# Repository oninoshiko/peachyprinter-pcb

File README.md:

This is just the production version of the Peachy Printer PCB, converted from Eagle format to Kicad.

Thanks to:

Rylan Grayston and the Peachy Team (for opening-sourceing, not just the 
					software, but the entire peachy design)

lachlanA (for the eagle to kicad conversion ULP)

Erich Heine (for the eagle half of the conversion)

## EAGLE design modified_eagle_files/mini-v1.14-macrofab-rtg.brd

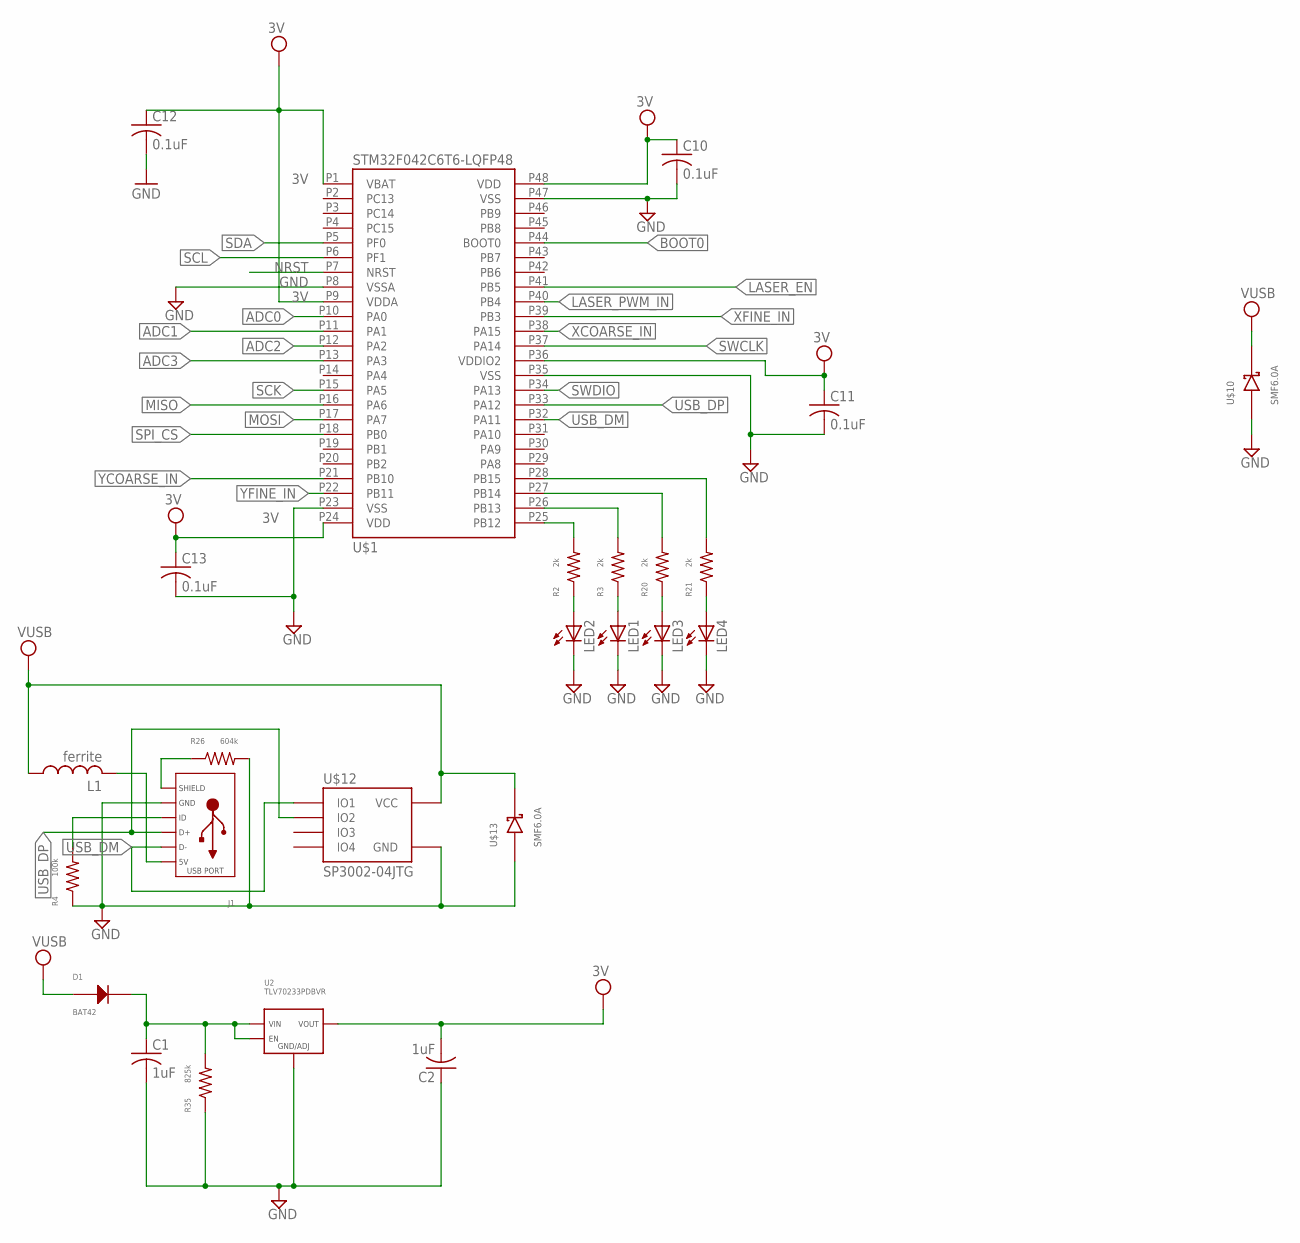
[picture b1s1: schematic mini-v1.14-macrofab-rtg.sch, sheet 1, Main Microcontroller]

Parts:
C1, C2: 1uF; C0603
C10, C11, C12, C13: 0.1uF; C0603
D1: BAT42; SOD-123
J1: USB_MICRO_RIGHT; MICROUSB-RIGHT
L1: ferrite; C0603
LED1, LED2, LED3, LED4: LEDCHIP-LED0603; CHIP-LED0603
R2, R3, R20, R21: 2k; R0603
R4: 100k; R0603
R26: 604k; R0603
R35: 825k; R0603
U2: TLV70233PDBVR; SOT-23-5
U$1: STM32F042C6T6-LQFP48; LQFP48
U$10, U$13: SMF6.0A; SOD123
U$12: SP3002-04JTG; SC70-6

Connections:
3V: C2.2, C10.1, C11.1, C12.1, C13.1, U2.P$5 (VOUT), U$1.P1 (VBAT), U$1.P9 (VDDA), U$1.P24 (VDD), U$1.P36 (VDDIO2), U$1.P48 (VDD); also elsewhere on the board
ADC0: U$1.P10 (PA0); also elsewhere on the board
ADC1: U$1.P11 (PA1); also elsewhere on the board
ADC2: U$1.P12 (PA2); also elsewhere on the board
ADC3: U$1.P13 (PA3); also elsewhere on the board
BOOT0: U$1.P44 (BOOT0); also elsewhere on the board
GND: C1.2, C2.1, C10.2, C11.2, C12.2, C13.2, J1.5 (GND), LED1.C, LED2.C, LED3.C, LED4.C, R4.P$1, R26.P$2, R35.P$1, U2.P$2 (GND/ADJ), U$1.P8 (VSSA), U$1.P23 (VSS), U$1.P35 (VSS), U$1.P47 (VSS), U$10.ANODE, U$12.P2 (GND), U$13.ANODE; also elsewhere on the board
LASER_EN: U$1.P41 (PB5); also elsewhere on the board
LASER_PWM_IN: U$1.P40 (PB4); also elsewhere on the board
MISO: U$1.P16 (PA6); also elsewhere on the board
MOSI: U$1.P17 (PA7); also elsewhere on the board
unnamed: R2.P$2, U$1.P25 (PB12)
unnamed: LED2.A, R2.P$1
unnamed: C1.1, D1.CATHODE, R35.P$2, U2.P$1 (VIN), U2.P$3 (EN)
unnamed: J1.4 (ID), R4.P$2
unnamed: LED1.A, R3.P$1
unnamed: R3.P$2, U$1.P26 (PB13)
unnamed: J1.1 (5V), L1.2
unnamed: J1.S1 (SLD), J1.S2 (SLD), J1.S3 (SLD), J1.S4 (SLD), J1.S5 (SLD), J1.S6 (SLD), R26.P$1
unnamed: LED3.A, R20.P$1
unnamed: LED4.A, R21.P$1
unnamed: R20.P$2, U$1.P27 (PB14)
unnamed: R21.P$2, U$1.P28 (PB15)
NRST: U$1.P7 (NRST); also elsewhere on the board
SCK: U$1.P15 (PA5); also elsewhere on the board
SCL: U$1.P6 (PF1); also elsewhere on the board
SDA: U$1.P5 (PF0); also elsewhere on the board
SPI_CS: U$1.P18 (PB0); also elsewhere on the board
SWCLK: U$1.P37 (PA14); also elsewhere on the board
SWDIO: U$1.P34 (PA13); also elsewhere on the board
USB_DM: J1.2 (D-), U$1.P32 (PA11), U$12.P1 (IO1)
USB_DP: J1.3 (D+), U$1.P33 (PA12), U$12.P3 (IO2)
VUSB: D1.ANODE, L1.1, U$10.CATHODE, U$12.P5 (VCC), U$13.CATHODE; also elsewhere on the board
XCOARSE_IN: U$1.P38 (PA15); also elsewhere on the board
XFINE_IN: U$1.P39 (PB3); also elsewhere on the board
YCOARSE_IN: U$1.P21 (PB10); also elsewhere on the board
YFINE_IN: U$1.P22 (PB11); also elsewhere on the board

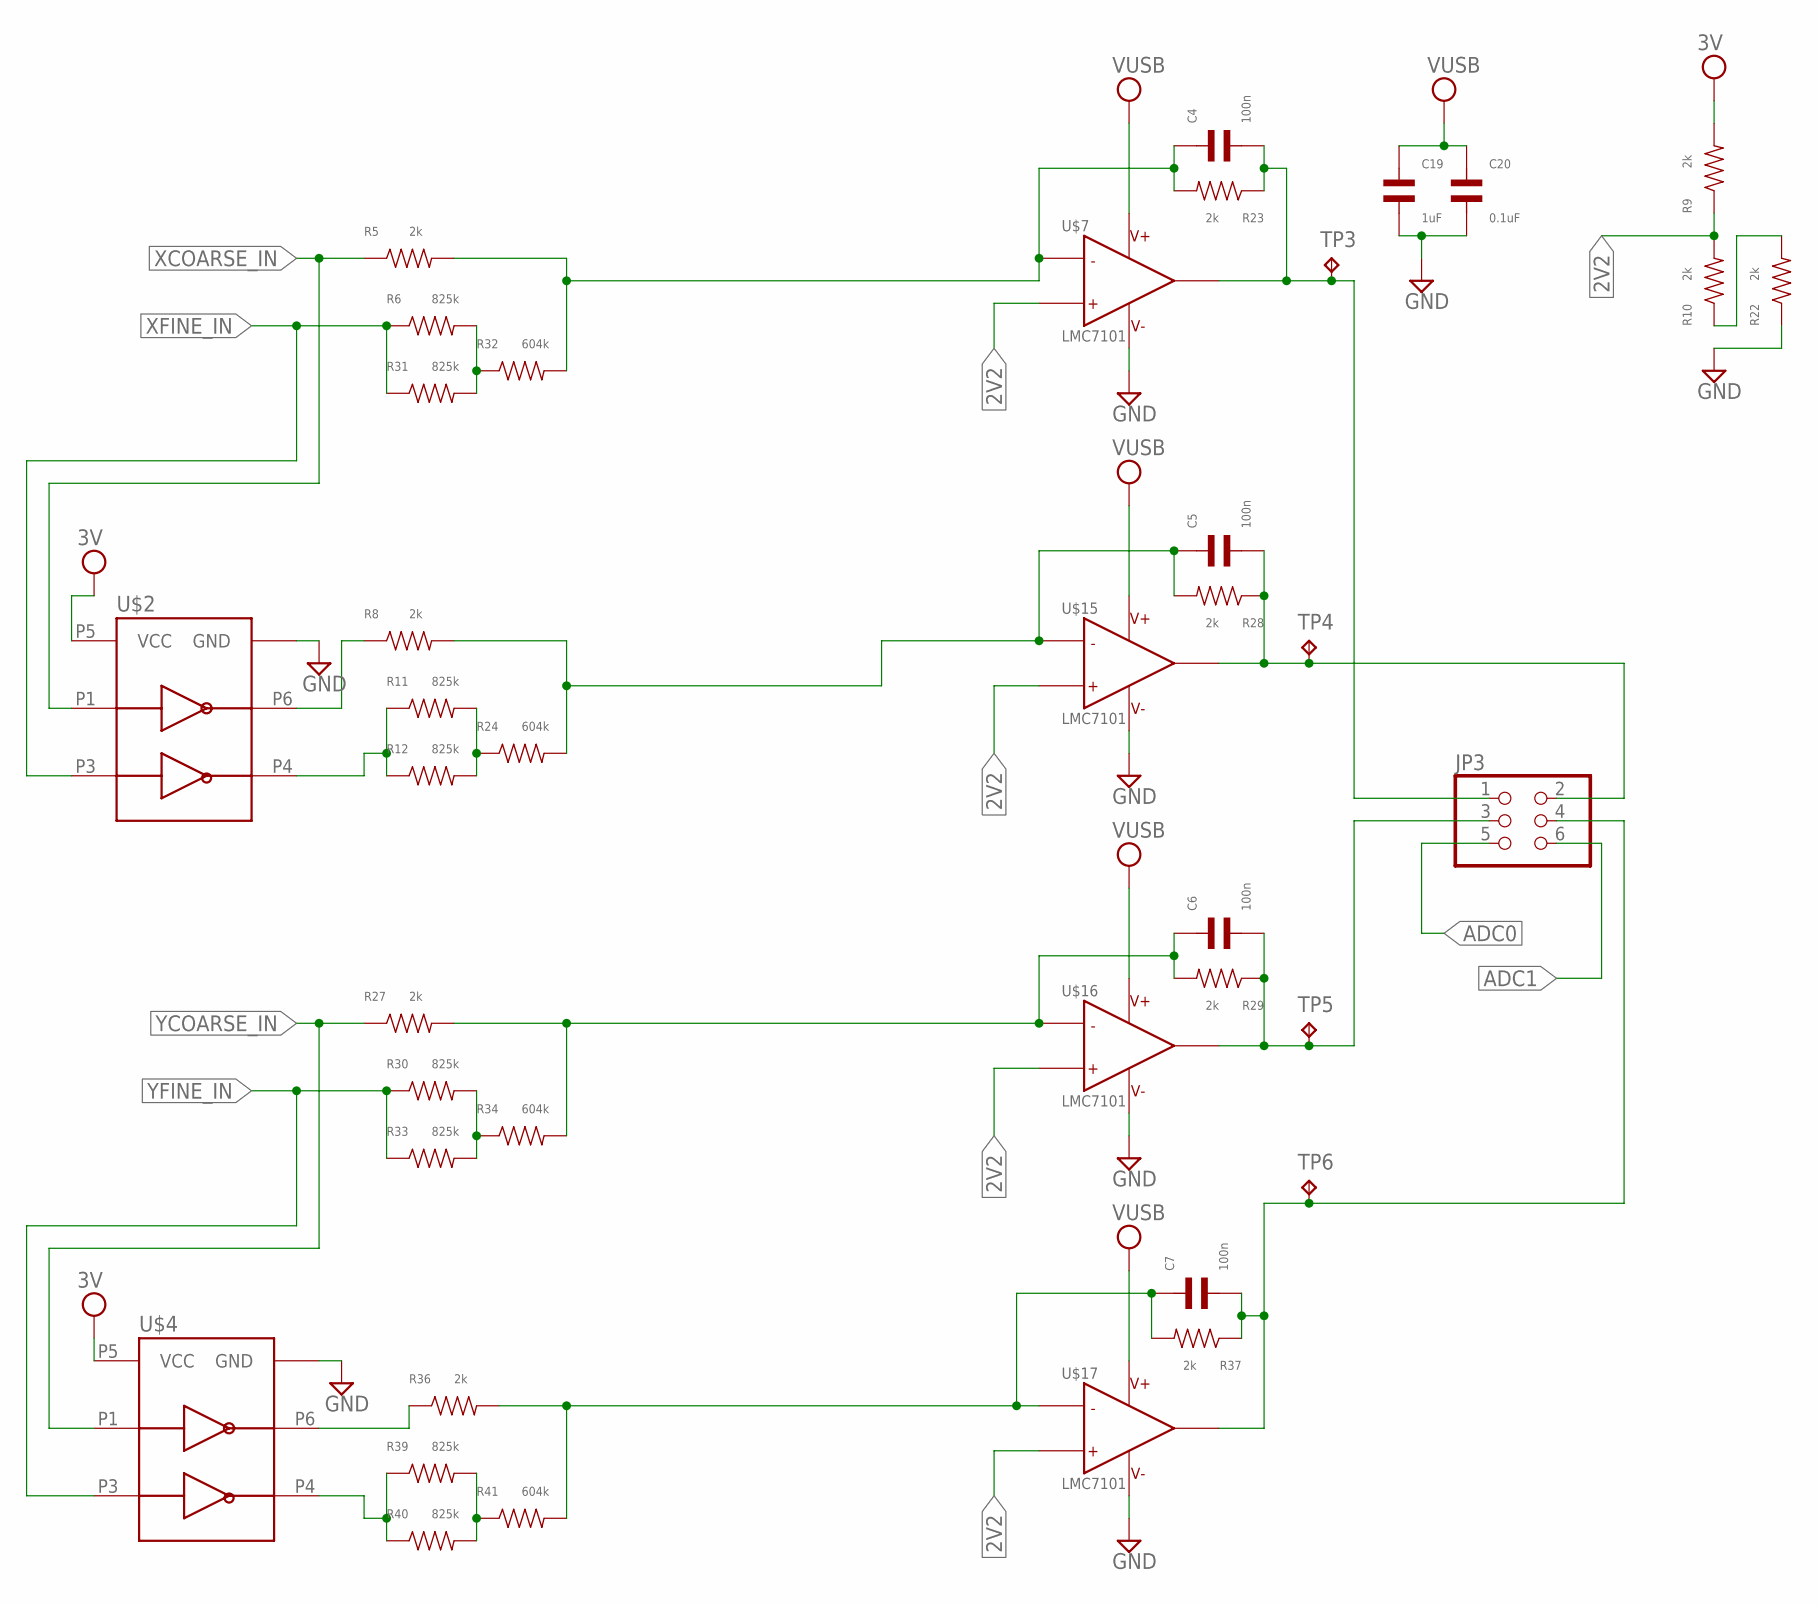
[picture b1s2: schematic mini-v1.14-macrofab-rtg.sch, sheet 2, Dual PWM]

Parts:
C4, C5, C6, C7: 100n; C0603
C19: 1uF; C0603
C20: 0.1uF; C0603
JP3: PINHD-2X3; 2X03
R5, R8, R9, R10, R22, R23, R27, R28, R29, R36, R37: 2k; R0603
R6, R11, R12, R30, R31, R33, R39, R40: 825k; R0603
R24, R32, R34, R41: 604k; R0603
TP3, TP4, TP5, TP6: TPB1,27; B1,27
U$2, U$4: NC7WZ14P6X; SC70-6
U$7, U$15, U$16, U$17: LMC7101; SOT23-5

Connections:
2V2: R9.P$1, R10.P$2, U$7.3, U$15.3, U$16.3, U$17.3
3V: R9.P$2, U$2.P5 (VCC), U$4.P5 (VCC); also elsewhere on the board
ADC0: JP3.5; also elsewhere on the board
ADC1: JP3.6; also elsewhere on the board
COARSE1: R8.P$1, U$2.P6 (Y1)
FINE1: R11.P$1, R12.P$1, U$2.P4 (Y2)
FINE3: R39.P$1, R40.P$1, U$4.P4 (Y2)
GND: C19.P$2, C20.P$2, R22.P$1, U$2.P2 (GND), U$4.P2 (GND), U$7.5, U$15.5, U$16.5, U$17.5; also elsewhere on the board
unnamed: R36.P$1, U$4.P6 (Y1)
unnamed: R11.P$2, R12.P$2, R24.P$1
unnamed: C5.P$1, R8.P$2, R24.P$2, R28.P$2, U$15.4
unnamed: R10.P$1, R22.P$2
unnamed: R30.P$2, R33.P$2, R34.P$1
unnamed: R6.P$2, R31.P$2, R32.P$1
unnamed: C6.P$1, R27.P$2, R29.P$2, R34.P$2, U$16.4
unnamed: R39.P$2, R40.P$2, R41.P$1
unnamed: C7.P$1, R36.P$2, R37.P$2, R41.P$2, U$17.4
OUT: C4.P$2, JP3.1, R23.P$1, TP3.TP, U$7.1
OUT1: C5.P$2, JP3.2, R28.P$1, TP4.TP, U$15.1
OUT2: C6.P$2, JP3.3, R29.P$1, TP5.TP, U$16.1
OUT3: C7.P$2, JP3.4, R37.P$1, TP6.TP, U$17.1
VUSB: C19.P$1, C20.P$1, U$7.2, U$15.2, U$16.2, U$17.2; also elsewhere on the board
XCOARSE_IN: R5.P$1, U$2.P1 (A1); also elsewhere on the board
XFINE_IN: R6.P$1, R31.P$1, U$2.P3 (A2); also elsewhere on the board
XSUM: C4.P$1, R5.P$2, R23.P$2, R32.P$2, U$7.4
YCOARSE_IN: R27.P$1, U$4.P1 (A1); also elsewhere on the board
YFINE_IN: R30.P$1, R33.P$1, U$4.P3 (A2); also elsewhere on the board

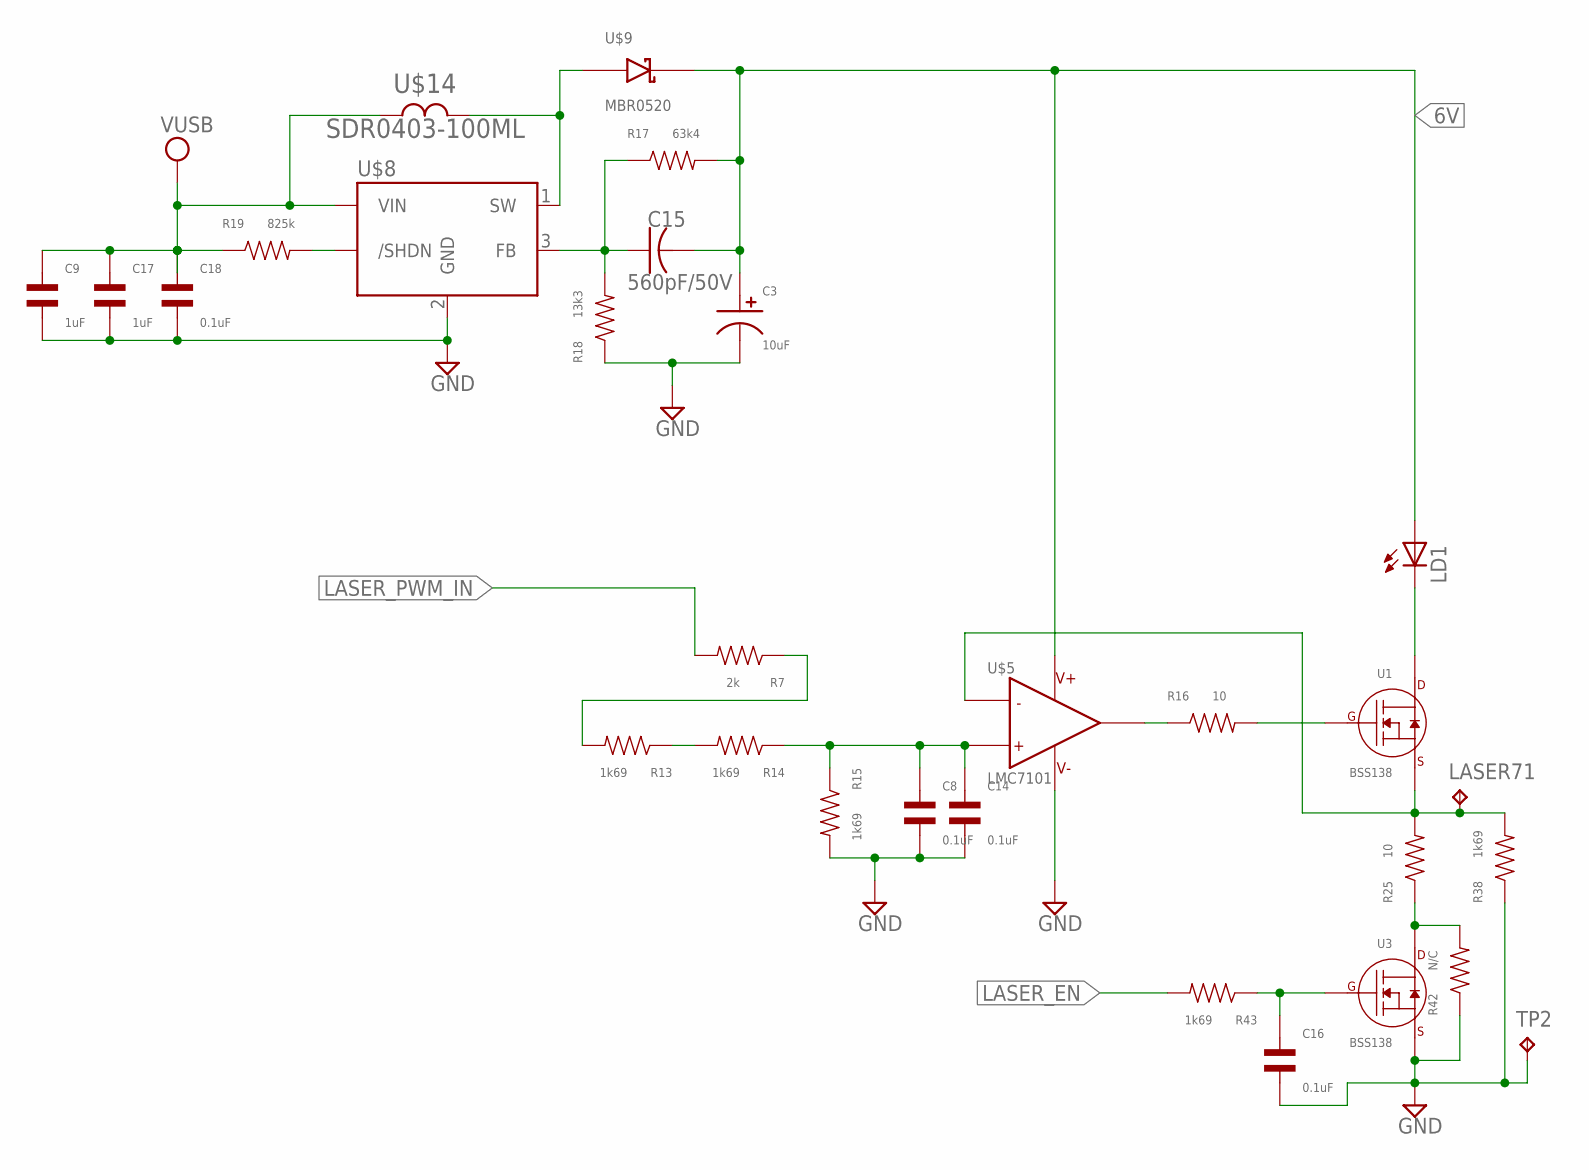
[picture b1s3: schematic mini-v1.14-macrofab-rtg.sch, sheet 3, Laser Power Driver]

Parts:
C3: 10uF; CP4MM
C8, C14, C16, C18: 0.1uF; C0603
C9, C17: 1uF; C0603
C15: 560pF/50V; C0603
LASER71: TPB2,54; B2,54
LD1: SCOTT_LASERDIODELD3; SCOTT_LASERDIODE3; MPN 3 x (0552-2-15-15-11-27-10-0)
R7: 2k; R0603
R13, R14, R15, R38, R43: 1k69; R0603
R16, R25: 10; R0603
R17: 63k4; R0603
R18: 13k3; R0603
R19: 825k; R0603
R42: N/C; R0603
TP2: GND; B2,54
U1, U3: BSS138; SOT-23-3
U$5: LMC7101; SOT23-5
U$8: LMR62014; SOT23-5
U$9: MBR0520; SOD123
U$14: SDR0403-100ML; SDR0403

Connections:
6V: C3.P$1, C15.2, LD1.P$1 (A), R17.P$2, U$5.2 (V+), U$9.CATHODE
GND: C3.P$2, C8.P$2, C9.P$2, C14.P$2, C16.P$2, C17.P$2, C18.P$2, R15.P$2, R18.P$1, R38.P$1, R42.P$1, TP2.TP, U3.P$2 (SOURCE), U$5.5 (V-), U$8.2 (GND); also elsewhere on the board
LASER_EN: R43.P$2; also elsewhere on the board
LASER_PWM_IN: R7.P$2; also elsewhere on the board
unnamed: R25.P$1, R42.P$2, U3.P$3 (DRAIN)
unnamed: R7.P$1, R13.P$2
unnamed: R13.P$1, R14.P$2
unnamed: C8.P$1, C14.P$1, R14.P$1, R15.P$1, U$5.3 (IN+)
unnamed: U$8.1 (SW), U$9.ANODE, U$14.P$2
unnamed: LD1.P$3 (C), U1.P$3 (DRAIN)
unnamed: LASER71.TP, R25.P$2, R38.P$2, U1.P$2 (SOURCE), U$5.4 (IN-)
unnamed: R16.P$2, U1.P$1 (GATE)
unnamed: R16.P$1, U$5.1 (OUT)
unnamed: C16.P$1, R43.P$1, U3.P$1 (GATE)
unnamed: C15.1, R17.P$1, R18.P$2, U$8.3 (FB)
unnamed: R19.P$2, U$8.4 (/SHDN)
VUSB: C9.P$1, C17.P$1, C18.P$1, R19.P$1, U$8.5 (VIN), U$14.P$1; also elsewhere on the board

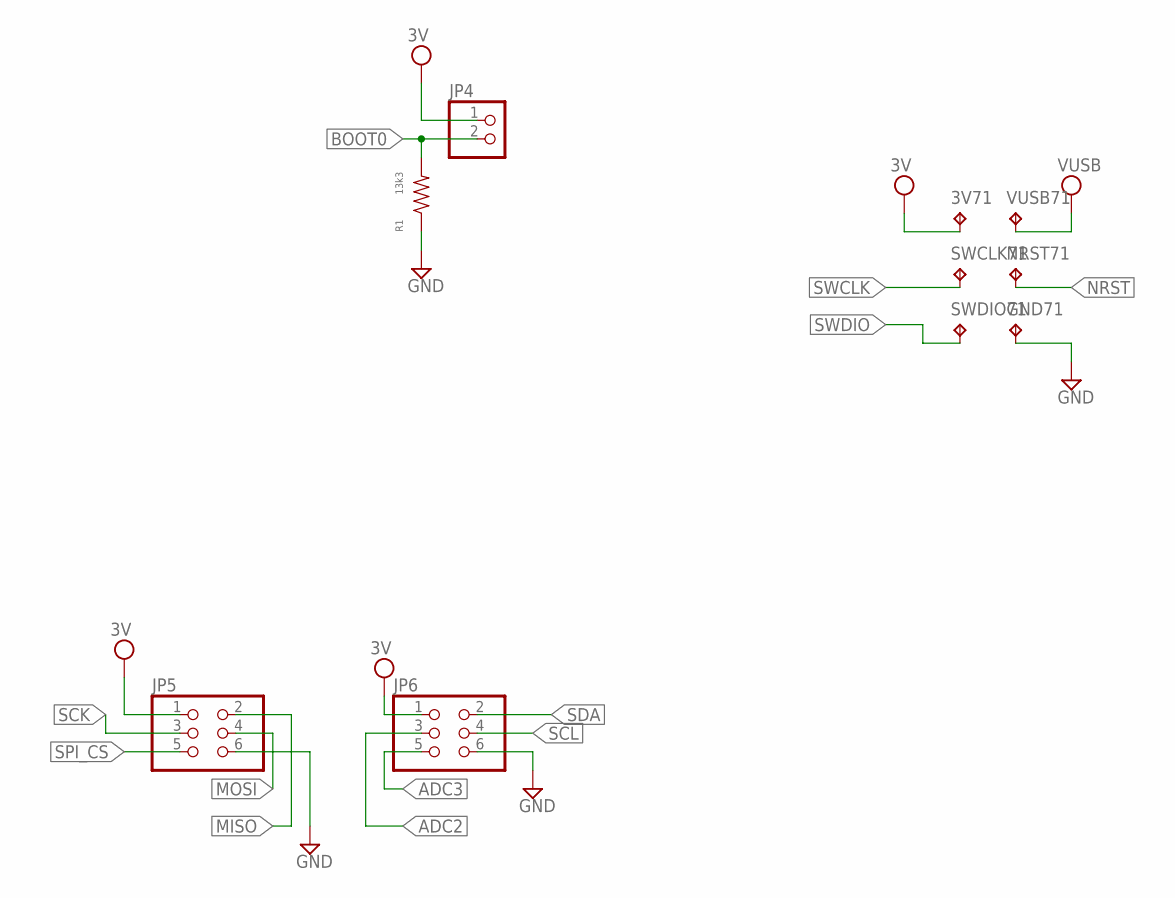
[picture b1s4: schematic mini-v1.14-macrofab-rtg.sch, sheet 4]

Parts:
3V71: TPB1,27; B1,27
GND71: TPB1,27; B1,27
JP4: PINHD-1X2; 1X02
JP5, JP6: PINHD-2X3; 2X03
NRST71: TPB1,27; B1,27
R1: 13k3; R0603
SWCLK71: TPB1,27; B1,27
SWDIO71: TPB1,27; B1,27
VUSB71: TPB1,27; B1,27

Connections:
3V: 3V71.TP, JP4.1, JP5.1, JP6.1; also elsewhere on the board
ADC2: JP6.3; also elsewhere on the board
ADC3: JP6.5; also elsewhere on the board
BOOT0: JP4.2, R1.P$2; also elsewhere on the board
GND: GND71.TP, JP5.6, JP6.6, R1.P$1; also elsewhere on the board
MISO: JP5.2; also elsewhere on the board
MOSI: JP5.4; also elsewhere on the board
NRST: NRST71.TP; also elsewhere on the board
SCK: JP5.3; also elsewhere on the board
SCL: JP6.4; also elsewhere on the board
SDA: JP6.2; also elsewhere on the board
SPI_CS: JP5.5; also elsewhere on the board
SWCLK: SWCLK71.TP; also elsewhere on the board
SWDIO: SWDIO71.TP; also elsewhere on the board
VUSB: VUSB71.TP; also elsewhere on the board

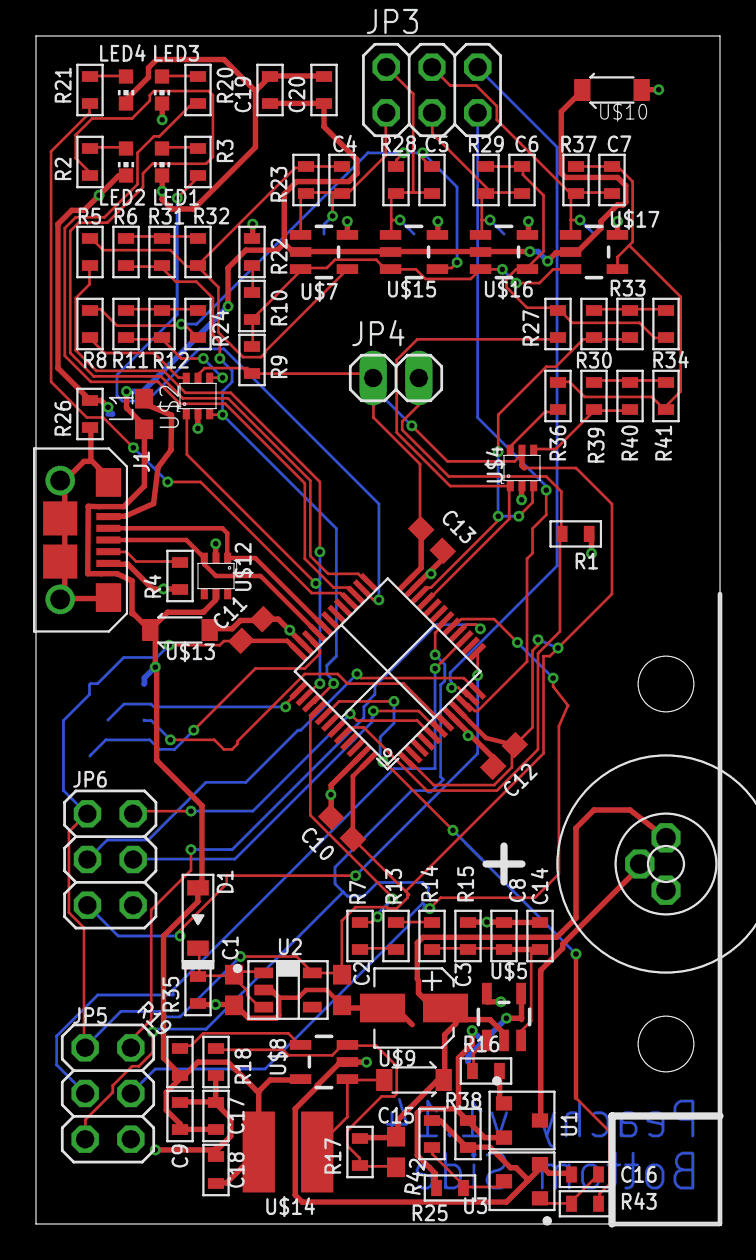
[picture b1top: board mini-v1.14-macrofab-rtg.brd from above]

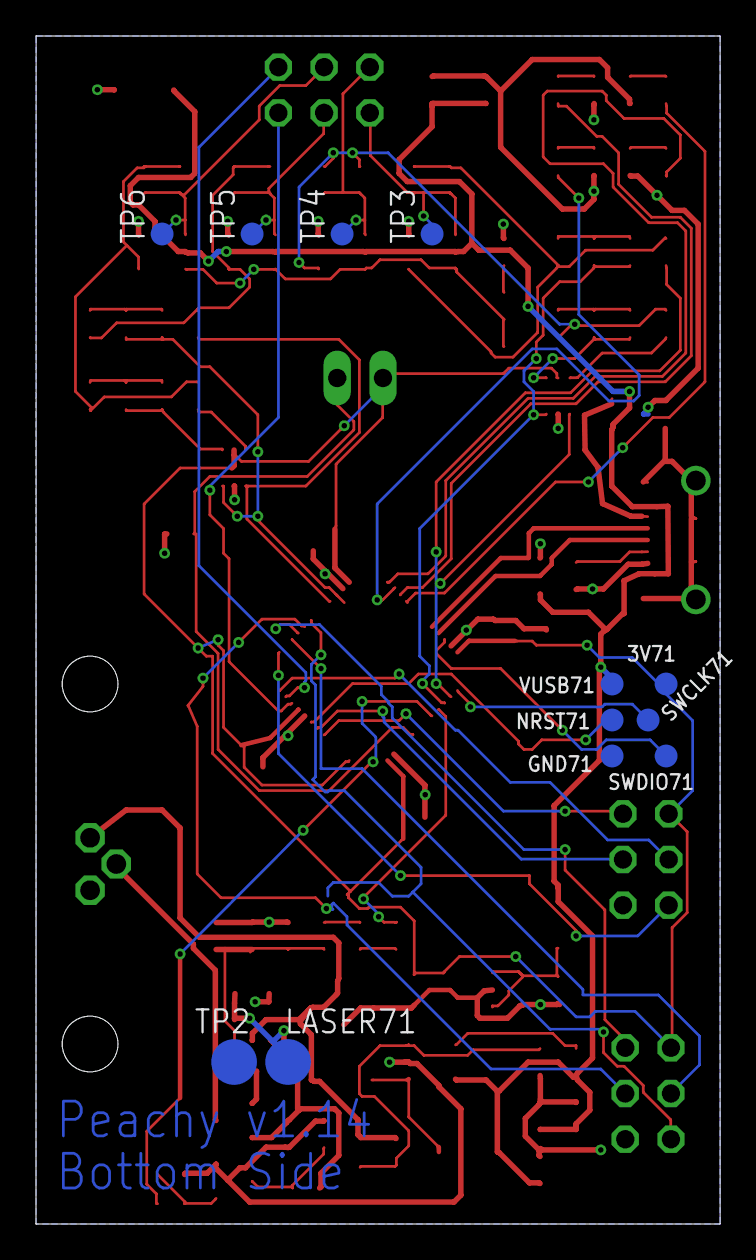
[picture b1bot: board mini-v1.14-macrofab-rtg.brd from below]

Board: 2 copper layers, 38.0 x 66.0 mm, 104 parts (12 on the bottom side), 68 nets.

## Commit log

2016-05-28 trim down to JUST 1.14 and convert to Kicad format
2016-05-28 mark unattached pins
2016-05-28 added .gitignore and fixed README.md
2016-05-28 footprints assigned
2016-05-28 Netlist generated and applied
